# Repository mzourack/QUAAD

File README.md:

# QUAAD
quad 4-step Eurorack CV sequencer

current version:

PCB     V1.1

Panel   V1.1

**Features**

Demo: https://www.youtube.com/watch?v=YCnnyX1JADY

This module is basically 4 independent 4-step sequencers. Each of them features a CV output (0-5V), a clock divider (1-2-3-4-5-7-8-12-16-32 divisions) and a pattern setting.
There are 6 patterns available, each one unique, as there are no repeating 4-step sequences between the looped patterns. Patterns can be changed per-sequence via a dedicated knob or via CV, aswell as globally using the MSTR PTRN knob, which basically adds a CV offset to each of the pattern CV inputs. The full range of patterns can be accesed via the pot corresponding to pattern changes of individual sequencers, the MSTR PTRN knob or via 0-5V CV. The patterns are looped, so that when, for example, you are on the last of the 6 patterns and add some positive CV offset, you will go back to the first one and then further on...
The patterns are determined by this variable in the Arduino code:

    int patterns[] = {1, 2, 3, 4,
                      1, 2, 4, 3,
                      2, 4, 1, 3,
                      3, 4, 2, 1,
                      4, 2, 3, 1,
                      4, 3, 2, 1};

The sequencer can be reset via a gate or manually using a button.
With nothing patched into the clock input, the module is clocked internally, the tempo can be set via a potentiometer. The clock output outputs this internal clock when no external clock input is patched in, otherwise, the incoming clock signal is buffered through this output.

The module is 22HP, no 5V source required from the rack.

**Hardware**

Not much to say here, the build is fairly straight forward. It features SMD components, the passives are 0603. 

**Firmware**

Complete step-by-step flashing guide available in the pdf file in this repository.

The Atmega328P is running on Arduino code - this means an Arduino bootloader needs to be flashed before the .ino code. To flash it, you can use an arduino (uno or nano for example) and a couple of jumper wires. I recommend to flash the module disconnected from the rack - the 5V needed to run the chip can be provided via the ICSP header. I used a USBASP from aliexpress, it works great but was quite hard to get working, so I cannot recommend it. If you do go down the USBASP route, note that you need to place a jumper on the programmer that slows down the data transfer frequency - a factory fresh atmega328p won't be able to accept the bootloader at USBASP default speed.

Here's the pinout of the ICSP header used for flashing the chip:

Finally, TX and RX pins are available on the back of the module. These can theoretically be used to debug the module, and could prove useful for testing new firmware. However, clock div out C and D have to be disabled in such case.

**License**

Shield: [![CC BY 4.0][cc-by-shield]][cc-by]

This work is licensed under a
[Creative Commons Attribution 4.0 International License][cc-by].

[![CC BY 4.0][cc-by-image]][cc-by]

[cc-by]: http://creativecommons.org/licenses/by/4.0/
[cc-by-image]: https://i.creativecommons.org/l/by/4.0/88x31.png
[cc-by-shield]: https://img.shields.io/badge/License-CC%20BY%204.0-lightgrey.svg

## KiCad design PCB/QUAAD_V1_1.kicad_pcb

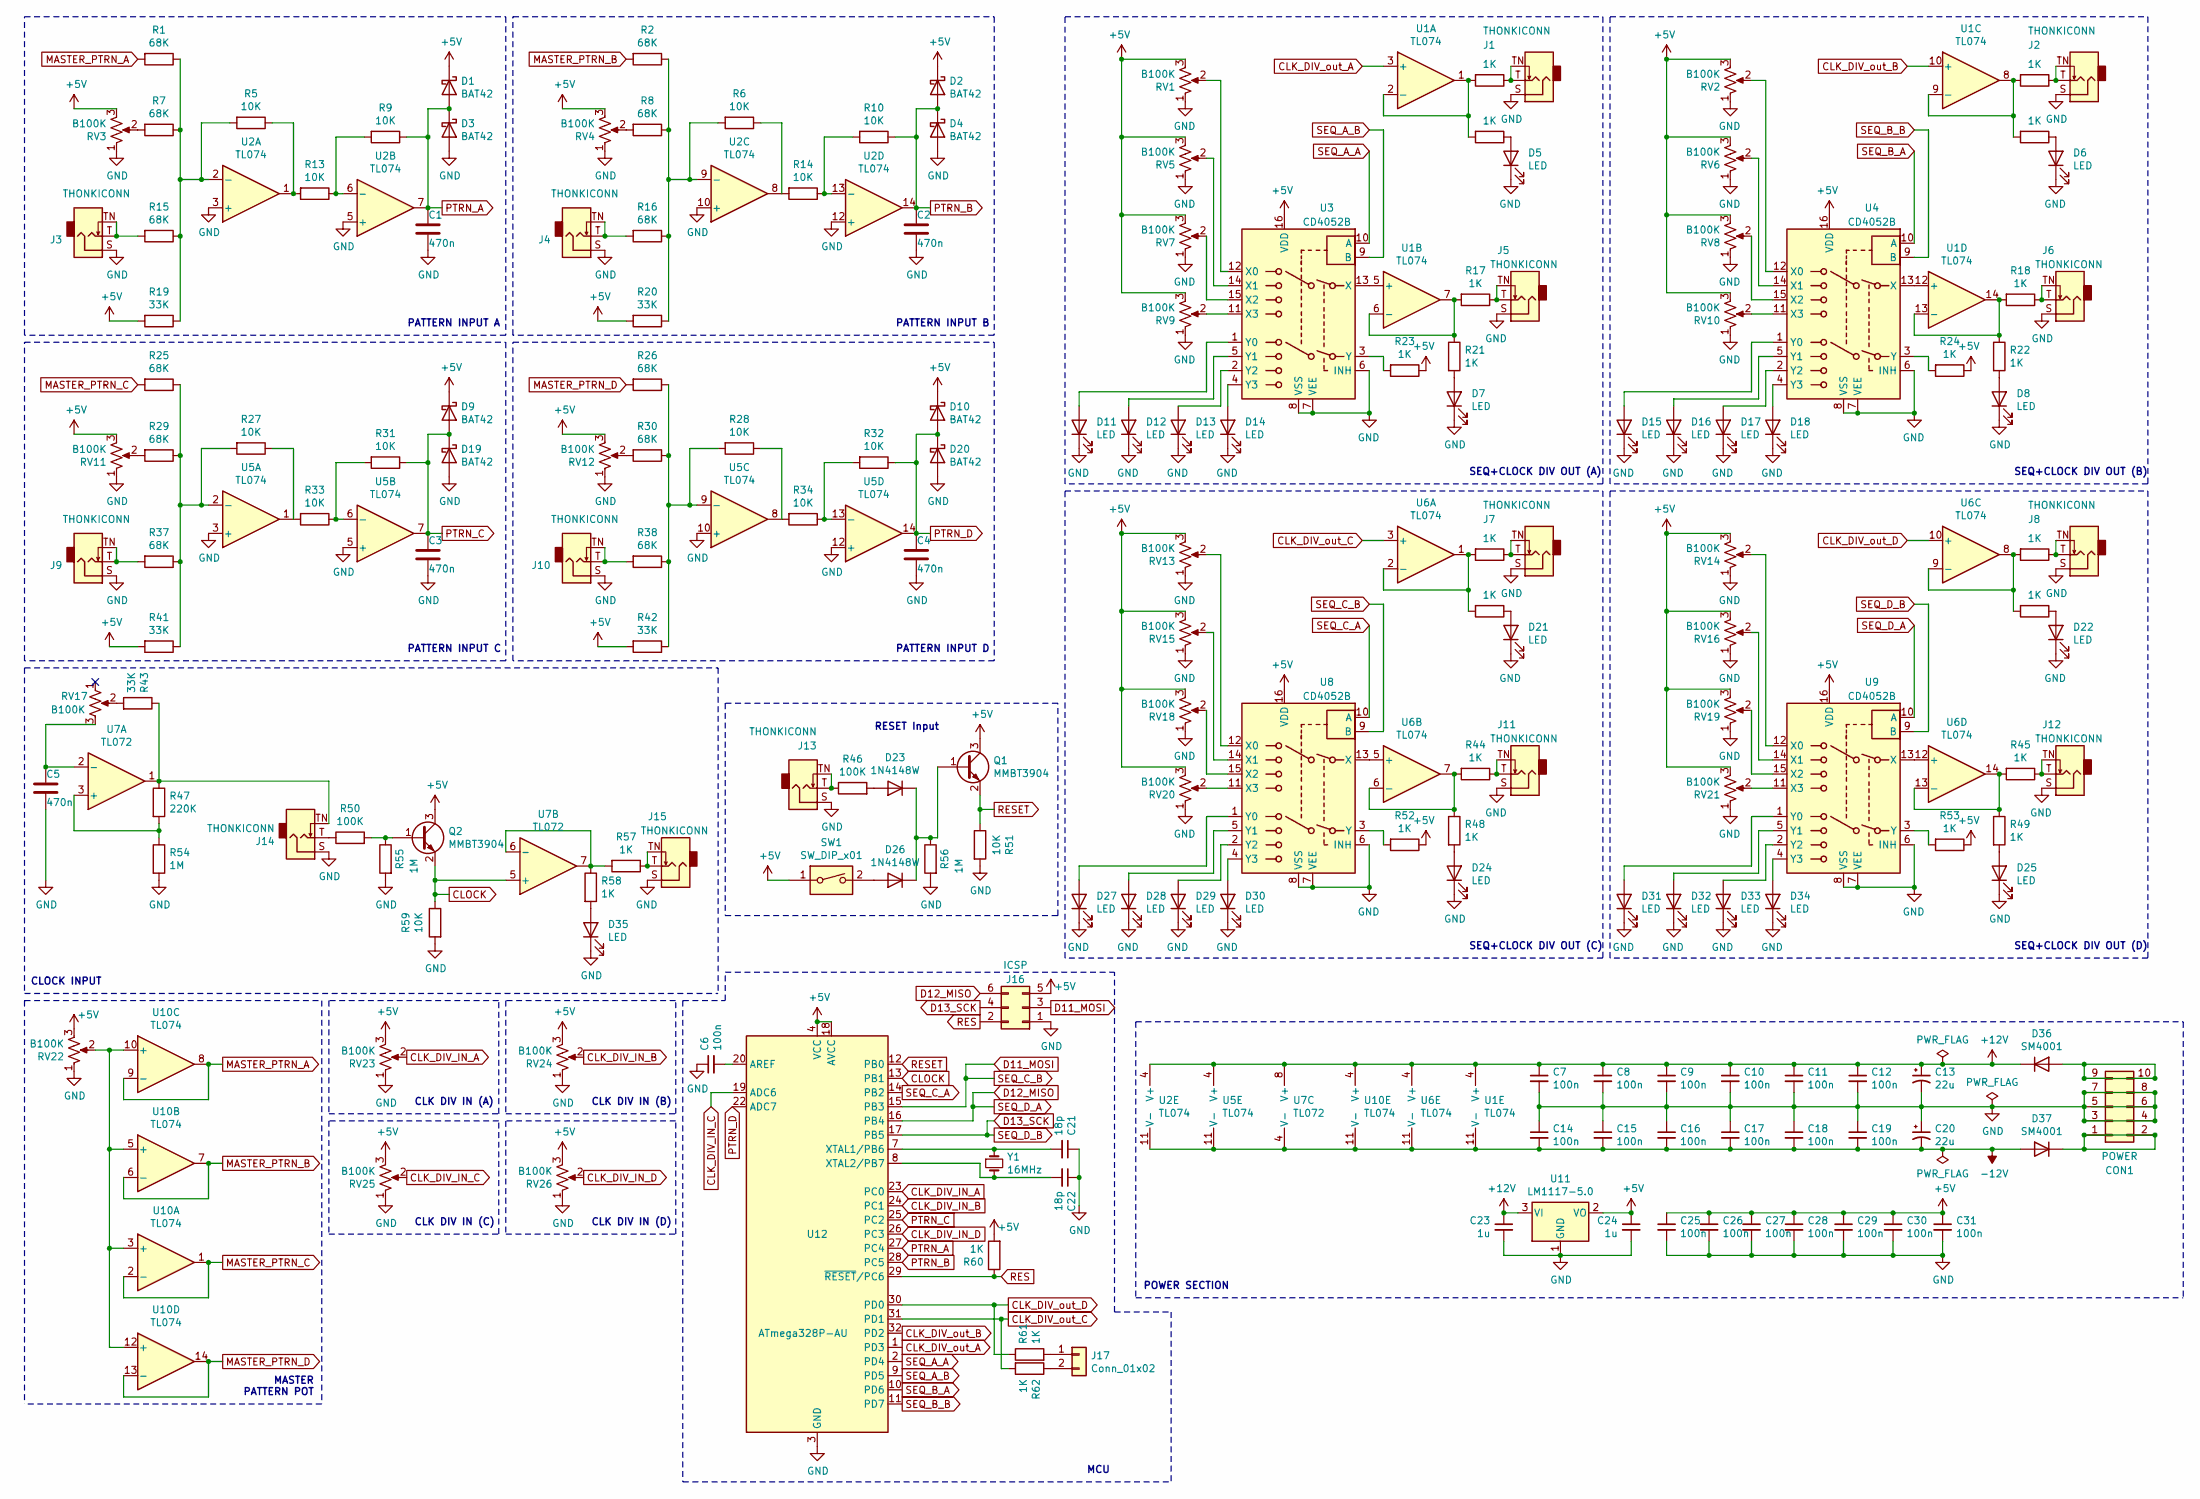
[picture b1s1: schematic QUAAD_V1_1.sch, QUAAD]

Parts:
C1, C2, C3, C4, C5: 470n; C_0603_1608Metric
C6, C7, C8, C9, C10, C11, C12, C14, C15, C16, C17, C18, C19, C25, C26, C27, C28, C29, C30, C31: 100n; C_0603_1608Metric
C13, C20: 22u; CP_Elec_5x5.8
C21, C22: 18p; C_0603_1608Metric
C23, C24: 1u; C_0603_1608Metric
CON1: POWER; IDC-Header_2x05_P2.54mm_Vertical
D1, D2, D3, D4, D9, D10, D19, D20: BAT42; D_SOD-123
D5, D6, D7, D8, D11, D12, D13, D14, D15, D16, D17, D18, D21, D22, D24, D25, D27, D28, D29, D30, D31, D32, D33, D34, D35: LED; CENTERED_FLAT_LED
D23, D26: 1N4148W; D_SOD-123
D36, D37: SM4001; D_SOD-123F
J1, J2, J3, J4, J5, J6, J7, J8, J9, J10, J11, J12, J13, J14, J15: THONKICONN; Jack_3.5mm_QingPu_WQP-PJ398SM_Vertical
J16: ICSP; PinHeader_2x03_P2.54mm_Vertical
J17: Conn_01x02; PinHeader_1x02_P2.54mm_Vertical
Q1, Q2: MMBT3904; SOT-23
R1, R2, R7, R8, R15, R16, R25, R26, R29, R30, R37, R38: 68K; R_0603_1608Metric
R3, R4, R11, R12, R17, R18, R21, R22, R23, R24, R35, R36, R39, R40, R44, R45, R48, R49, R52, R53, R57, R58, R60, R61, R62: 1K; R_0603_1608Metric
R5, R6, R9, R10, R13, R14, R27, R28, R31, R32, R33, R34, R51, R59: 10K; R_0603_1608Metric
R19, R20, R41, R42, R43: 33K; R_0603_1608Metric
R46, R50: 100K; R_0603_1608Metric
R47: 220K; R_0603_1608Metric
R54, R55, R56: 1M; R_0603_1608Metric
RV1, RV2, RV3, RV4, RV5, RV6, RV7, RV8, RV9, RV10, RV11, RV12, RV13, RV14, RV15, RV16, RV17, RV18, RV19, RV20, RV21, RV22, RV23, RV24, RV25, RV26: B100K; Potentiometer_Alpha_RD901F-40-00D_Single_Vertical
SW1: SW_DIP_x01; SW_PUSH_6mm
U1, U2, U5, U6, U10: TL074; SOIC-14_3.9x8.7mm_P1.27mm
U3, U4, U8, U9: CD4052B; SOP-16_4.55x10.3mm_P1.27mm
U7: TL072; SOIC-8_3.9x4.9mm_P1.27mm
U11: LM1117-5.0; SOT-223-3_TabPin2
U12: ATmega328P-AU; TQFP-32_7x7mm_P0.8mm
Y1: 16MHz; Crystal_SMD_HC49-SD

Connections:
+5V: C24.1, C25.1, C26.1, C27.1, C28.1, C29.1, C30.1, C31.1, D1.1 (K), D2.1 (K), D9.1 (K), D10.1 (K), J16.5, Q1.3 (C), Q2.3 (C), R19.2, R20.2, R23.1, R24.1, R41.2, R42.2, R52.1, R53.1, R60.2, RV1.3, RV2.3, RV3.3, RV4.3, RV5.3, RV6.3, RV7.3, RV8.3, RV9.3, RV10.3, RV11.3, RV12.3, RV13.3, RV14.3, RV15.3, RV16.3, RV18.3, RV19.3, RV20.3, RV21.3, RV22.3, RV23.3, RV24.3, RV25.3, RV26.3, SW1.1, U3.16 (VDD), U4.16 (VDD), U8.16 (VDD), U9.16 (VDD), U11.2 (VO), U12.4 (VCC), U12.6 (VCC), U12.18 (AVCC)
+12V: C7.1, C8.1, C9.1, C10.1, C11.1, C12.1, C13.1, C23.1, D36.1 (K), U1.4 (V+), U2.4 (V+), U5.4 (V+), U6.4 (V+), U7.8 (V+), U10.4 (V+), U11.3 (VI)
-12V: C14.2, C15.2, C16.2, C17.2, C18.2, C19.2, C20.2, D37.2 (A), U1.11 (V-), U2.11 (V-), U5.11 (V-), U6.11 (V-), U7.4 (V-), U10.11 (V-)
CLK_DIV_IN_A: RV23.2, U12.23 (PC0)
CLK_DIV_IN_B: RV24.2, U12.24 (PC1)
CLK_DIV_IN_C: RV25.2, U12.19 (ADC6)
CLK_DIV_IN_D: RV26.2, U12.26 (PC3)
CLK_DIV_out_A: U1.3 (+), U12.1 (PD3)
CLK_DIV_out_B: U1.10 (+), U12.32 (PD2)
CLK_DIV_out_C: R62.2, U6.3 (+), U12.31 (PD1)
CLK_DIV_out_D: R61.1, U6.10 (+), U12.30 (PD0)
CLOCK: Q2.2 (E), R59.1, U7.5 (+), U12.13 (PB1)
D11_MOSI: J16.3, U8.9 (B), U12.15 (PB3)
D12_MISO: J16.6, U9.10 (A), U12.16 (PB4)
D13_SCK: J16.4, U9.9 (B), U12.17 (PB5)
GND: C1.2, C2.2, C3.2, C4.2, C5.2, C6.1, C7.2, C8.2, C9.2, C10.2, C11.2, C12.2, C13.2, C14.1, C15.1, C16.1, C17.1, C18.1, C19.1, C20.1, C21.1, C22.1, C23.2, C24.2, C25.2, C26.2, C27.2, C28.2, C29.2, C30.2, C31.2, CON1.3, CON1.4, CON1.5, CON1.6, CON1.7, CON1.8, D3.2 (A), D4.2 (A), D5.1 (K), D6.1 (K), D7.1 (K), D8.1 (K), D11.1 (K), D12.1 (K), D13.1 (K), D14.1 (K), D15.1 (K), D16.1 (K), D17.1 (K), D18.1 (K), D19.2 (A), D20.2 (A), D21.1 (K), D22.1 (K), D24.1 (K), D25.1 (K), D27.1 (K), D28.1 (K), D29.1 (K), D30.1 (K), D31.1 (K), D32.1 (K), D33.1 (K), D34.1 (K), D35.1 (K), J1.S, J2.S, J3.S, J4.S, J5.S, J6.S, J7.S, J8.S, J9.S, J10.S, J11.S, J12.S, J13.S, J14.S, J15.S, J16.1, R51.2, R54.2, R55.2, R56.2, R59.2, RV1.1, RV2.1, RV3.1, RV4.1, RV5.1, RV6.1, RV7.1, RV8.1, RV9.1, RV10.1, RV11.1, RV12.1, RV13.1, RV14.1, RV15.1, RV16.1, RV18.1, RV19.1, RV20.1, RV21.1, RV22.1, RV23.1, RV24.1, RV25.1, RV26.1, U2.3 (+), U2.5 (+), U2.10 (+), U2.12 (+), U3.6 (INH), U3.7 (VEE), U3.8 (VSS), U4.6 (INH), U4.7 (VEE), U4.8 (VSS), U5.3 (+), U5.5 (+), U5.10 (+), U5.12 (+), U8.6 (INH), U8.7 (VEE), U8.8 (VSS), U9.6 (INH), U9.7 (VEE), U9.8 (VSS), U11.1 (GND), U12.3 (GND), U12.5 (GND), U12.21 (GND)
MASTER_PTRN_A: R1.2, U10.8, U10.9 (-)
MASTER_PTRN_B: R2.2, U10.6 (-), U10.7
MASTER_PTRN_C: R25.2, U10.1, U10.2 (-)
MASTER_PTRN_D: R26.2, U10.13 (-), U10.14
unnamed: C5.1, RV17.3, U7.2 (-)
unnamed: C6.2, U12.20 (AREF)
unnamed: C21.2, U12.7 (XTAL1/PB6), Y1.1
unnamed: C22.2, U12.8 (XTAL2/PB7), Y1.2
unnamed: CON1.1, CON1.2, D37.1 (K)
unnamed: CON1.9, CON1.10, D36.2 (A)
unnamed: D5.2 (A), R11.1
unnamed: D6.2 (A), R12.1
unnamed: D7.2 (A), R21.2
unnamed: D8.2 (A), R22.2
unnamed: D11.2 (A), U3.1 (Y0)
unnamed: D12.2 (A), U3.5 (Y1)
unnamed: D13.2 (A), U3.2 (Y2)
unnamed: D14.2 (A), U3.4 (Y3)
unnamed: D15.2 (A), U4.1 (Y0)
unnamed: D16.2 (A), U4.5 (Y1)
unnamed: D17.2 (A), U4.2 (Y2)
unnamed: D18.2 (A), U4.4 (Y3)
unnamed: D21.2 (A), R39.1
unnamed: D22.2 (A), R40.1
unnamed: D23.1 (K), D26.1 (K), Q1.1 (B), R56.1
unnamed: D23.2 (A), R46.2
unnamed: D24.2 (A), R48.2
unnamed: D25.2 (A), R49.2
unnamed: D26.2 (A), SW1.2
unnamed: D27.2 (A), U8.1 (Y0)
unnamed: D28.2 (A), U8.5 (Y1)
unnamed: D29.2 (A), U8.2 (Y2)
unnamed: D30.2 (A), U8.4 (Y3)
unnamed: D31.2 (A), U9.1 (Y0)
unnamed: D32.2 (A), U9.5 (Y1)
unnamed: D33.2 (A), U9.2 (Y2)
unnamed: D34.2 (A), U9.4 (Y3)
unnamed: D35.2 (A), R58.2
unnamed: J1.T, J1.TN, R3.1
unnamed: J2.T, J2.TN, R4.1
unnamed: J3.T, J3.TN, R15.2
unnamed: J4.T, J4.TN, R16.2
unnamed: J5.T, J5.TN, R17.1
unnamed: J6.T, J6.TN, R18.1
unnamed: J7.T, J7.TN, R35.1
unnamed: J8.T, J8.TN, R36.1
unnamed: J9.T, J9.TN, R37.2
unnamed: J10.T, J10.TN, R38.2
unnamed: J11.T, J11.TN, R44.1
unnamed: J12.T, J12.TN, R45.1
unnamed: J13.T, J13.TN, R46.1
unnamed: J14.T, R50.1
unnamed: J14.TN, R43.1, R47.1, U7.1
unnamed: J15.T, J15.TN, R57.1
unnamed: J17.1, R61.2
unnamed: J17.2, R62.1
unnamed: Q2.1 (B), R50.2, R55.1
unnamed: R1.1, R5.2, R7.1, R15.1, R19.1, U2.2 (-)
unnamed: R7.2, RV3.2
unnamed: R8.2, RV4.2
unnamed: R10.2, R14.1, U2.13 (-)
unnamed: R3.2, R11.2, U1.1, U1.2 (-)
unnamed: R4.2, R12.2, U1.8, U1.9 (-)
unnamed: R9.2, R13.1, U2.6 (-)
unnamed: R5.1, R13.2, U2.1
unnamed: R6.1, R14.2, U2.8
unnamed: R2.1, R6.2, R8.1, R16.1, R20.1, U2.9 (-)
unnamed: R17.2, R21.1, U1.6 (-), U1.7
unnamed: R18.2, R22.1, U1.13 (-), U1.14
unnamed: R23.2, U3.3 (Y)
unnamed: R24.2, U4.3 (Y)
unnamed: R25.1, R27.2, R29.1, R37.1, R41.1, U5.2 (-)
unnamed: R26.1, R28.2, R30.1, R38.1, R42.1, U5.9 (-)
unnamed: R27.1, R33.2, U5.1
unnamed: R28.1, R34.2, U5.8
unnamed: R29.2, RV11.2
unnamed: R30.2, RV12.2
unnamed: R31.2, R33.1, U5.6 (-)
unnamed: R32.2, R34.1, U5.13 (-)
unnamed: R35.2, R39.2, U6.1, U6.2 (-)
unnamed: R36.2, R40.2, U6.8, U6.9 (-)
unnamed: R43.2, RV17.2
unnamed: R44.2, R48.1, U6.6 (-), U6.7
unnamed: R45.2, R49.1, U6.13 (-), U6.14
unnamed: R47.2, R54.1, U7.3 (+)
unnamed: R52.2, U8.3 (Y)
unnamed: R53.2, U9.3 (Y)
unnamed: R57.2, R58.1, U7.6 (-), U7.7
unnamed: RV1.2, U3.12 (X0)
unnamed: RV2.2, U4.12 (X0)
unnamed: RV5.2, U3.14 (X1)
unnamed: RV6.2, U4.14 (X1)
unnamed: RV7.2, U3.15 (X2)
unnamed: RV8.2, U4.15 (X2)
unnamed: RV9.2, U3.11 (X3)
unnamed: RV10.2, U4.11 (X3)
unnamed: RV13.2, U8.12 (X0)
unnamed: RV14.2, U9.12 (X0)
unnamed: RV15.2, U8.14 (X1)
unnamed: RV16.2, U9.14 (X1)
unnamed: RV18.2, U8.15 (X2)
unnamed: RV19.2, U9.15 (X2)
unnamed: RV20.2, U8.11 (X3)
unnamed: RV21.2, U9.11 (X3)
unnamed: RV22.2, U10.3 (+), U10.5 (+), U10.10 (+), U10.12 (+)
unnamed: U1.5 (+), U3.13 (X)
unnamed: U1.12 (+), U4.13 (X)
unnamed: U6.5 (+), U8.13 (X)
unnamed: U6.12 (+), U9.13 (X)
PTRN_A: C1.1, D1.2 (A), D3.1 (K), R9.1, U2.7, U12.27 (PC4)
PTRN_B: C2.1, D2.2 (A), D4.1 (K), R10.1, U2.14, U12.28 (PC5)
PTRN_C: C3.1, D9.2 (A), D19.1 (K), R31.1, U5.7, U12.25 (PC2)
PTRN_D: C4.1, D10.2 (A), D20.1 (K), R32.1, U5.14, U12.22 (ADC7)
RES: J16.2, R60.1, U12.29 (~RESET~/PC6)
RESET: Q1.2 (E), R51.1, U12.12 (PB0)
SEQ_A_A: U3.10 (A), U12.2 (PD4)
SEQ_A_B: U3.9 (B), U12.9 (PD5)
SEQ_B_A: U4.10 (A), U12.10 (PD6)
SEQ_B_B: U4.9 (B), U12.11 (PD7)
SEQ_C_A: U8.10 (A), U12.14 (PB2)

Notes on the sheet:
CLK DIV IN (A)
PATTERN INPUT A
CLK DIV IN (B)
CLK DIV IN (C)
CLK DIV IN (D)
PATTERN INPUT B
PATTERN INPUT C
PATTERN INPUT D
RESET Input
SEQ+CLOCK DIV OUT (D)
SEQ+CLOCK DIV OUT (C)
SEQ+CLOCK DIV OUT (B)
SEQ+CLOCK DIV OUT (A)
MCU
CLOCK INPUT
POWER SECTION
MASTER PATTERN POT

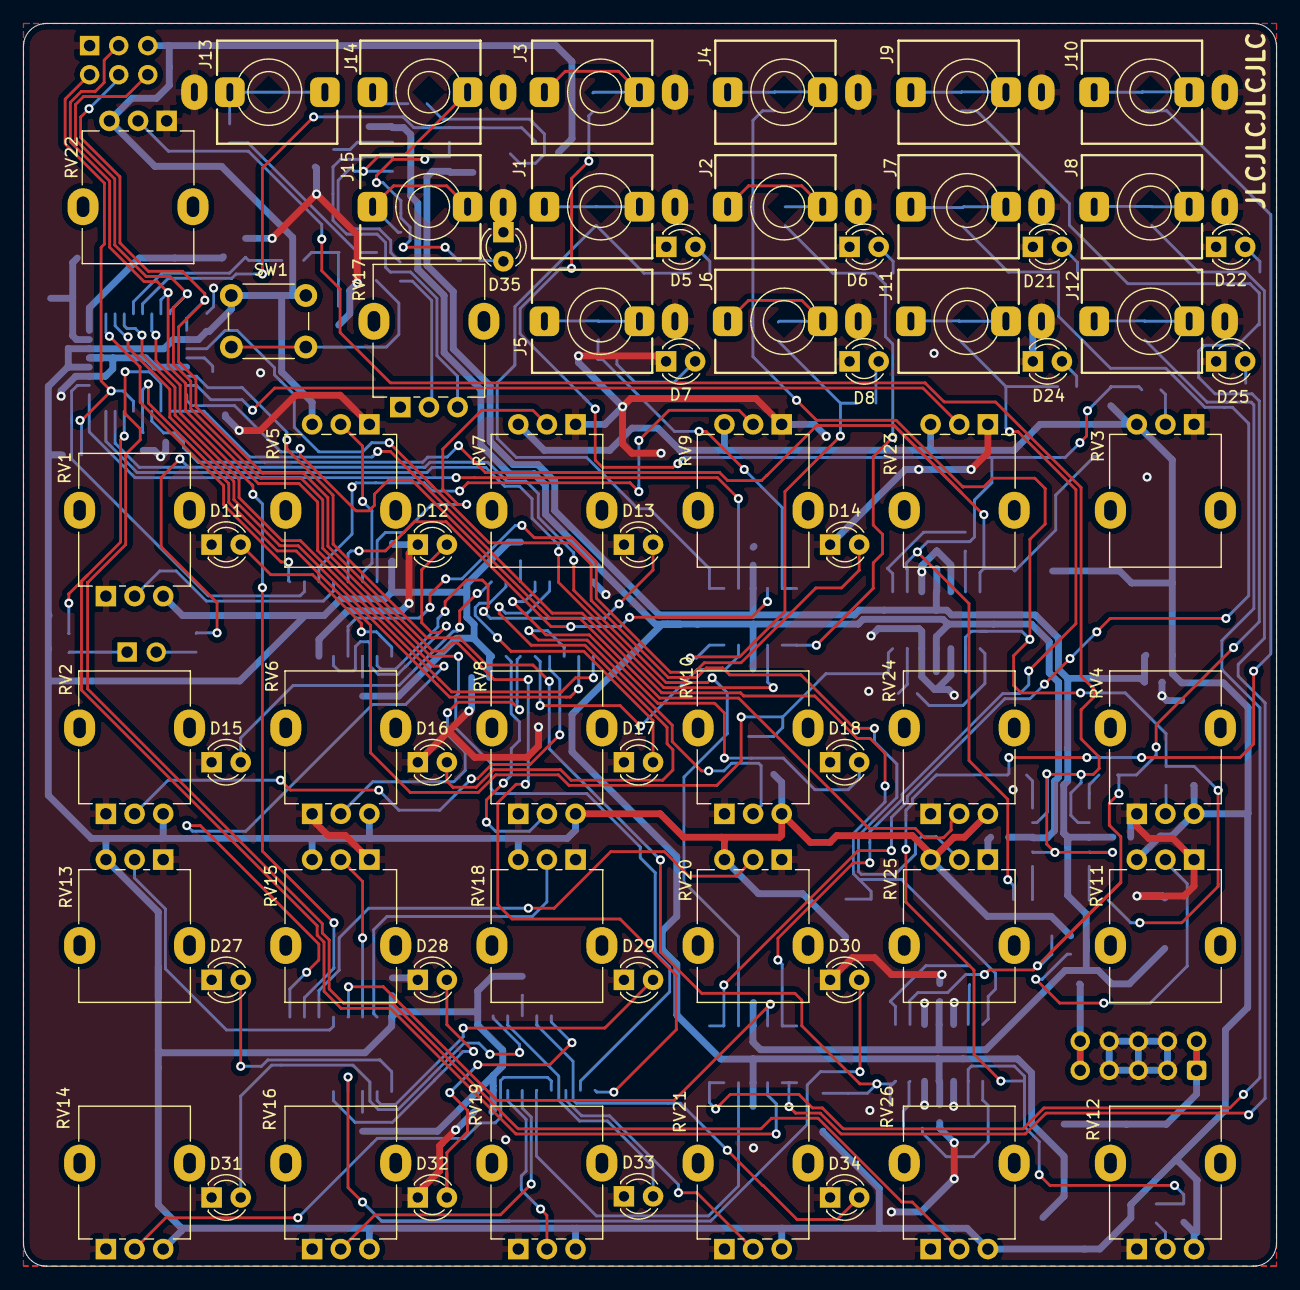
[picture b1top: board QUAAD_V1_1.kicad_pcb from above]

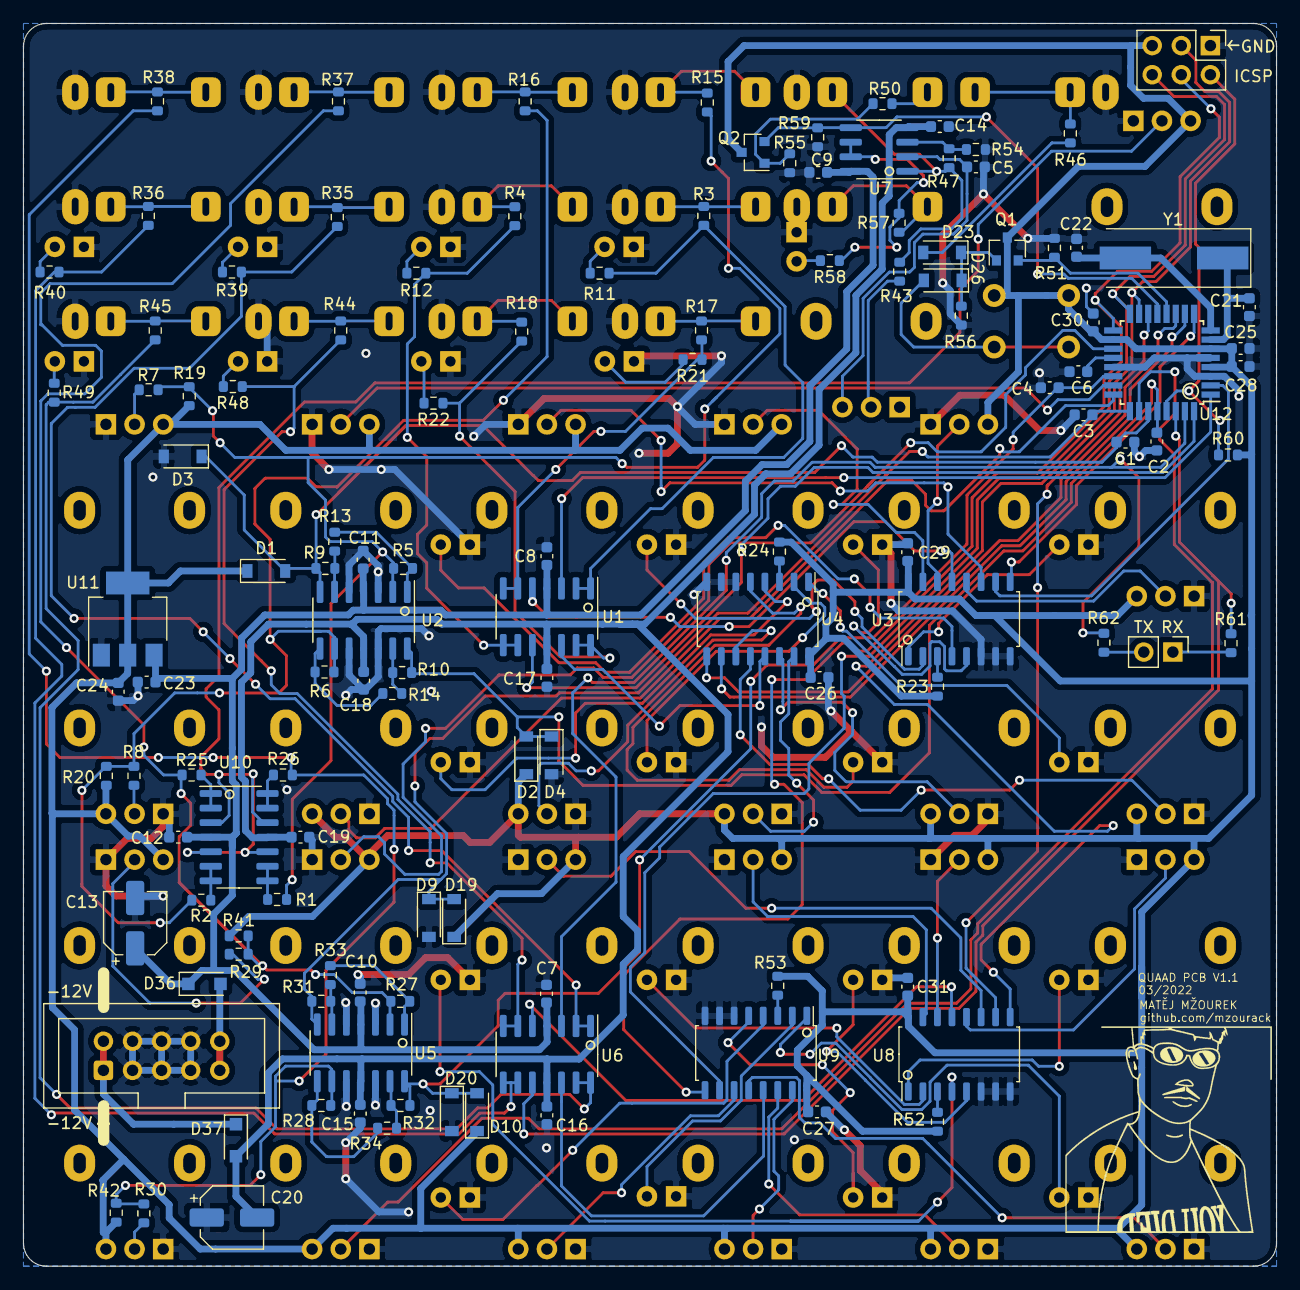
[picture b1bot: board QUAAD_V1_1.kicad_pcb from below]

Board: 2 copper layers, 109.4 x 108.5 mm, 191 parts (123 on the bottom side), 136 nets.

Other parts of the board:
Ref**: Val**; logo_18

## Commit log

2022-04-12 Add files via upload
    PDF schematic was outdated
2022-12-26 Add files via upload
    flashing guide
2023-11-16 readme update
